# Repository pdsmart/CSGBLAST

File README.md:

# perlblast / CSGBLAST
a Perl-Tk implementation of galblast/atfblast that uses the parport device (even via USB!)

A parallel/USB port GAL programmer which supports a wider range of GAL's than can be found in available commercial products. It has been written in Perl, runs on Linux/Windows/Mac (where the Perl eco system is available) and
provides a custom hardware design, CSGBlaster, which advances on the galblast/atfblast concept. 

The main project can be found on Kees Schoenmaker's repository: https://github.com/kees1948/perlblast.

This repository provides the design for an adapter to program GAL26V12 devices which being plentiful on Ebay (to say they went out of production a long time ago) but very little (ie. none) programmer support.

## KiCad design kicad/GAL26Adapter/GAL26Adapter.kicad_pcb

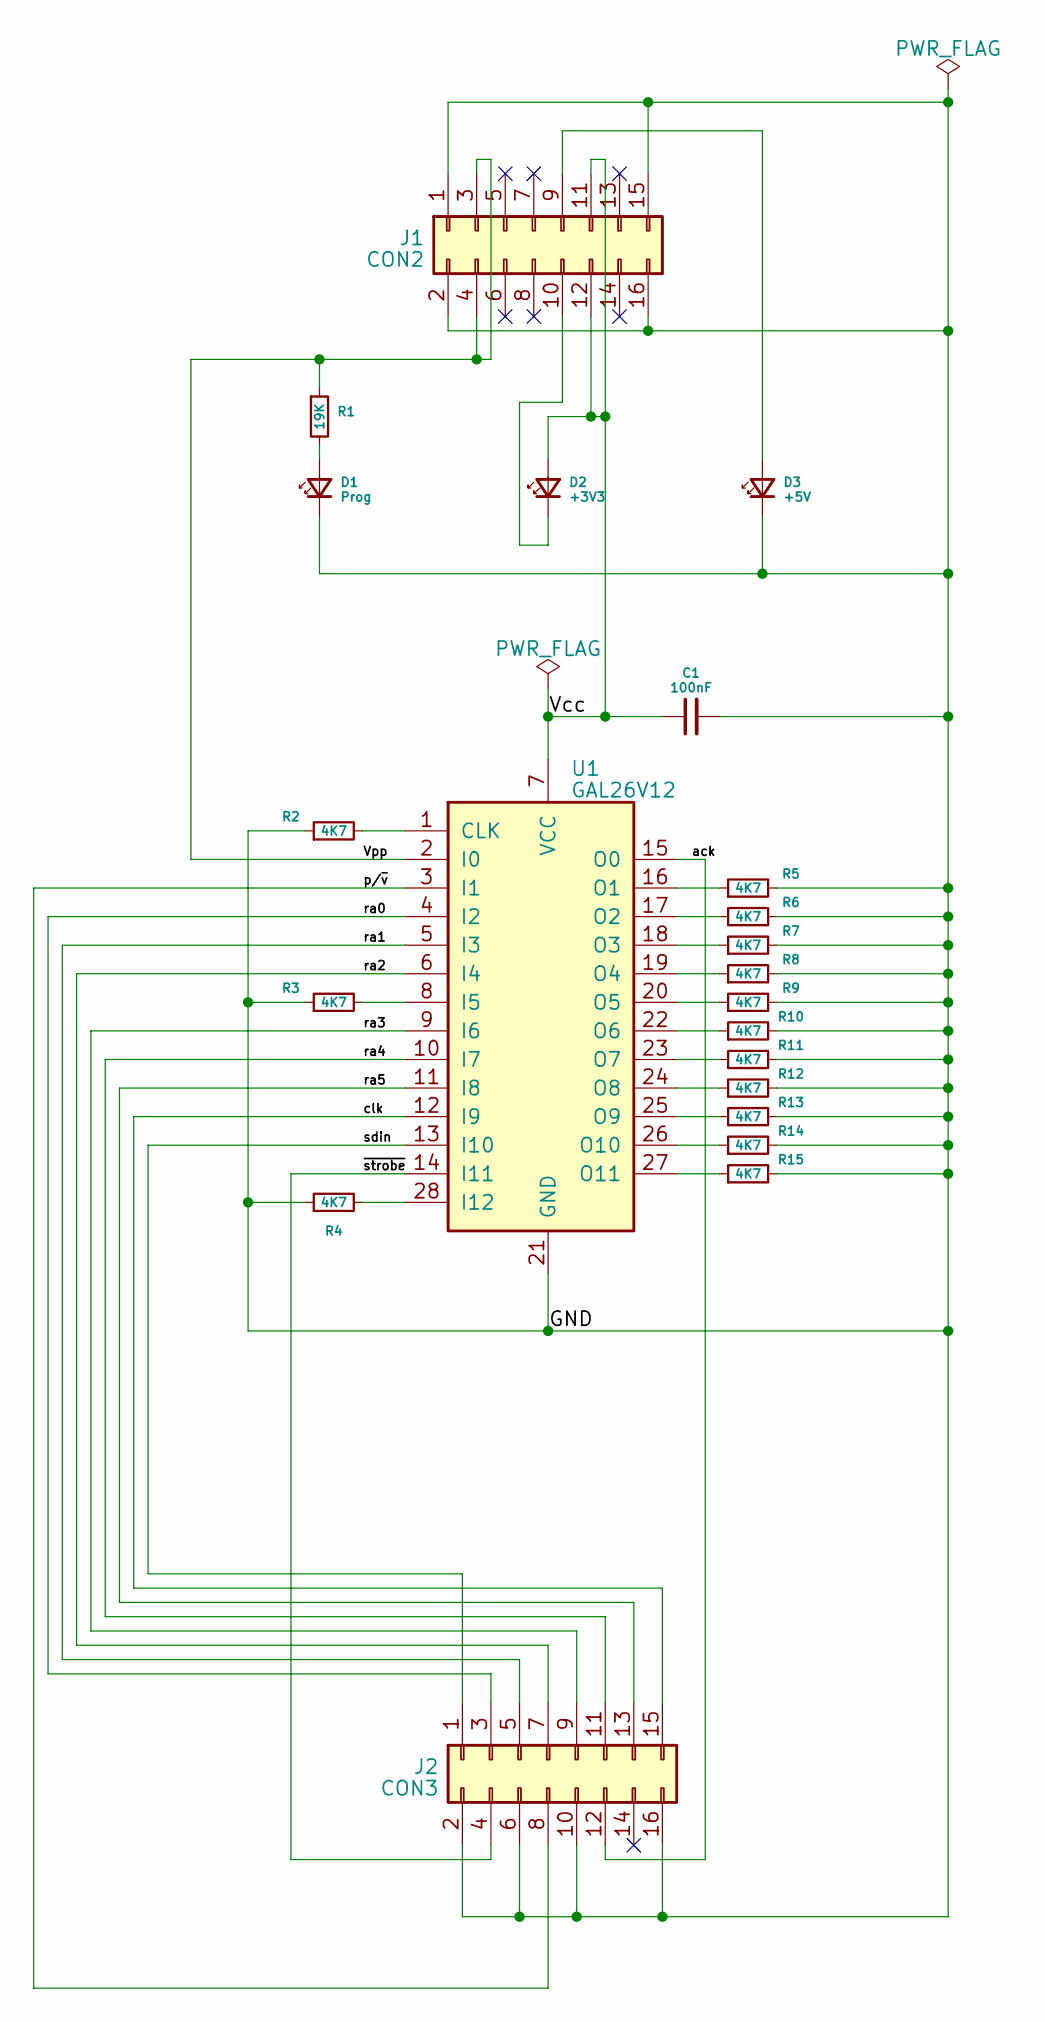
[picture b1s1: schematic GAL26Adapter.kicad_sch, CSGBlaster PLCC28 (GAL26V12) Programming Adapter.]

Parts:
C1: 100nF; C_0805_2012Metric
D1: Prog; LED_0603_1608Metric
D2: +3V3; LED_0603_1608Metric
D3: +5V; LED_0603_1608Metric
J1: CON2; PinHeader_2x08_P2.54mm_Vertical
J2: CON3; PinHeader_2x08_P2.54mm_Vertical
R1: 19K; R_0805_2012Metric
R2, R3, R4, R5, R6, R7, R8, R9, R10, R11, R12, R13, R14, R15: 4K7; R_0805_2012Metric
U1: GAL26V12; PLCC-28_THT-Socket

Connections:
/GND: C1.2, D1.1 (K), D3.1 (K), J1.1, J1.2, J1.15, J1.16, J2.2, J2.6, J2.10, J2.16, R2.1, R3.1, R4.1, R5.2, R6.2, R7.2, R8.2, R9.2, R10.2, R11.2, R12.2, R13.2, R14.2, R15.2, U1.21 (GND)
/Vcc: C1.1, D2.2 (A), J1.11, J1.12, U1.7 (VCC)
/Vpp: J1.3, J1.4, R1.1, U1.2 (I0)
/ack: J2.12, U1.15 (O0)
/clk: J2.15, U1.12 (I9)
/p/~v: J2.8, U1.3 (I1)
/ra0: J2.3, U1.4 (I2)
/ra1: J2.5, U1.5 (I3)
/ra2: J2.7, U1.6 (I4)
/ra3: J2.9, U1.9 (I6)
/ra4: J2.11, U1.10 (I7)
/ra5: J2.13, U1.11 (I8)
/sdin: J2.1, U1.13 (I10)
/~strobe: J2.4, U1.14 (I11)
unnamed: D1.2 (A), R1.2
unnamed: D2.1 (K), J1.10
unnamed: D3.2 (A), J1.9
unnamed: R2.2, U1.1 (CLK)
unnamed: R3.2, U1.8 (I5)
unnamed: R4.2, U1.28 (I12)
unnamed: R5.1, U1.16 (O1)
unnamed: R6.1, U1.17 (O2)
unnamed: R7.1, U1.18 (O3)
unnamed: R8.1, U1.19 (O4)
unnamed: R9.1, U1.20 (O5)
unnamed: R10.1, U1.22 (O6)
unnamed: R11.1, U1.23 (O7)
unnamed: R12.1, U1.24 (O8)
unnamed: R13.1, U1.25 (O9)
unnamed: R14.1, U1.26 (O10)
unnamed: R15.1, U1.27 (O11)

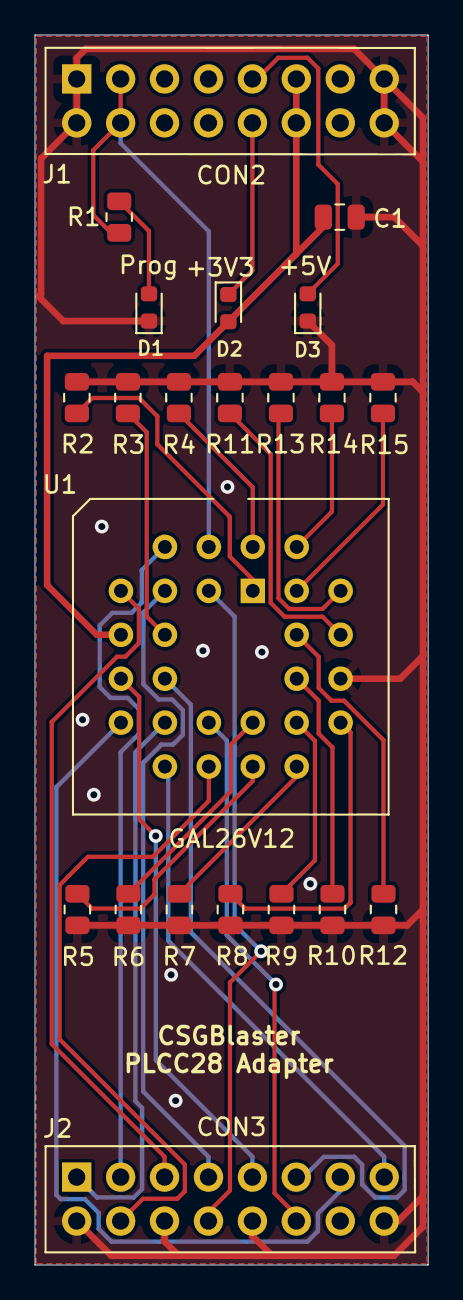
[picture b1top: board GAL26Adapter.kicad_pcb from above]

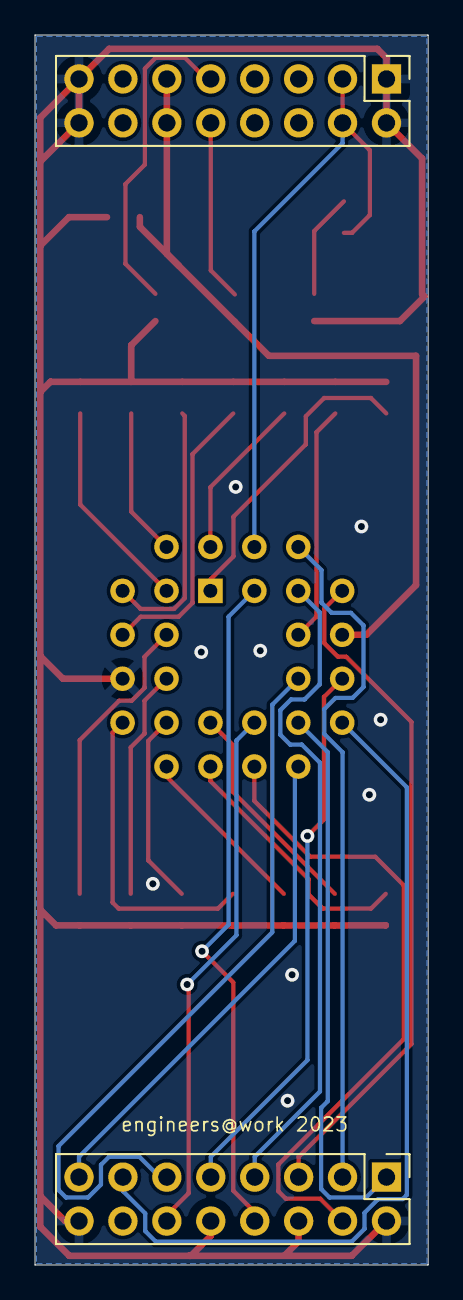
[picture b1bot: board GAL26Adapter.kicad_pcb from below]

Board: 2 copper layers, 22.7 x 71.1 mm, 22 parts (2 on the bottom side), 31 nets.

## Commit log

2023-04-18 Repo setup
2023-04-18 First release of adapter
2023-04-18 Typo
2023-04-18 Linguist update
